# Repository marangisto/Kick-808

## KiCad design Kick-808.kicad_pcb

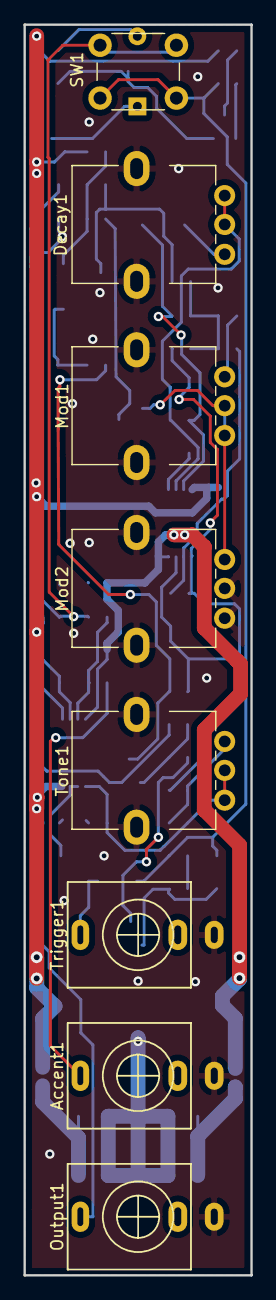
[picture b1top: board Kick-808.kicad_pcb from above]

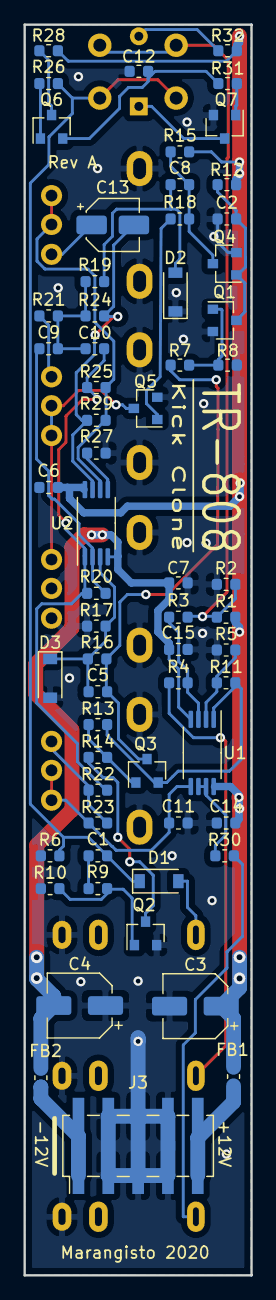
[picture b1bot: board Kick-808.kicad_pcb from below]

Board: 2 copper layers, 19.3 x 106.5 mm, 70 parts (62 on the bottom side), 42 nets.

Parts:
Accent1: AudioJack2_SwitchT; PJ398SM
C1, C2, C6, C7, C14, C15: 100n; C_0603_1608Metric
C3, C4: 22u; CP_Elec_5x5.4
C5, C9, C10: 15n; C_0603_1608Metric
C8: 33n; C_0603_1608Metric
C11: 22n; C_0603_1608Metric
C12: 1u; C_0603_1608Metric
C13: 10u; CP_Elec_4x5.8
D1, D2, D3: 1N4148; D_SOD-123
Decay1: 100k; AlpsRK09K
FB1, FB2: Ferrite_Bead; L_0603_1608Metric
J3: Conn_02x05_Odd_Even; PinHeader_2x05_P2.54mm_Vertical_SMD
Mod1: 10k; AlpsRK09K
Mod2: 100k; AlpsRK09K
Output1: AudioJack2_SwitchT; PJ398SM
Q1, Q2, Q4, Q5, Q6, Q7: BC847; SOT-23
Q3: BC857; SOT-23
R1: 2k2; R_0603_1608Metric
R2: 1k5; R_0603_1608Metric
R3: 200k; R_0603_1608Metric
R4, R31: 47k; R_0603_1608Metric
R5, R6, R11, R16, R18, R23, R26: 100k; R_0603_1608Metric
R7: 8k2; R_0603_1608Metric
R8: 2k7; R_0603_1608Metric
R9, R15: 22k; R_0603_1608Metric
R10, R14, R25, R29: 10k; R_0603_1608Metric
R12, R19, R20: 1M; R_0603_1608Metric
R13, R17, R27: 4k7; R_0603_1608Metric
R21, R28, R32: 1k; R_0603_1608Metric
R22: 220; R_0603_1608Metric
R24: 470k; R_0603_1608Metric
R30: 680; R_0603_1608Metric
SW1: SW_Push_LED; SW_PUSH_LED_6mm
Tone1: 100k; AlpsRK09K
Trigger1: AudioJack2_SwitchT; PJ398SM
U1, U2: TL072; TSSOP-8_4.4x3mm_P0.65mm

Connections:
5V: R1.2, R2.1, R3.2, SW1.1
+12V: C3.1, C6.2, C14.2, FB1.1, R1.1, R12.1, R15.1, R28.1, R32.1, U1.8, U2.8
-12V: C4.2, C7.1, C15.1, FB2.1, U1.4, U2.4
GND: Accent1.S, C2.2, C3.2, C4.1, C6.1, C7.2, C11.2, C12.2, C14.1, C15.2, D2.1, D3.2, J3.3, J3.4, J3.5, J3.6, J3.7, J3.8, Mod2.2, Mod2.3, Output1.S, Q1.2, Q2.2, Q4.2, Q5.2, Q7.2, R2.2, R5.2, R6.2, R8.1, R10.2, R17.2, R27.2, Trigger1.S
unnamed: Accent1.T, R4.2
unnamed: C1.1, R9.1
unnamed: C2.1, Q1.3, Q4.1, R12.2
unnamed: C5.1, D3.1, R16.1, R17.1, U2.3
unnamed: C5.2, Q3.3, R7.2, R16.2
unnamed: C8.1, D2.2, R19.2
unnamed: C8.2, Q4.3, R15.2, R18.2
unnamed: C9.2, R20.2, U2.2
unnamed: C10.1, R20.1, R22.1, R25.2, U2.1
unnamed: C9.1, C10.2, R19.1, R21.1, R24.2
unnamed: C11.1, R23.2, Tone1.2, Tone1.3, U1.5
unnamed: C12.1, Q6.2, R31.2
unnamed: C13.1, Decay1.3
unnamed: C13.2, R24.1, R29.1, U2.7
unnamed: D1.2, Trigger1.T
unnamed: Decay1.1, Decay1.2, R25.1, R29.2, U2.6
unnamed: FB1.2, J3.9, J3.10
unnamed: FB2.2, J3.1, J3.2
unnamed: Mod1.1, R21.2
unnamed: Mod1.2, Mod1.3, Mod2.1, Q5.3
unnamed: Output1.T, R30.1
unnamed: Q1.1, R7.1, R8.2
unnamed: Q2.1, R9.2, R10.1
unnamed: Q2.3, R14.2
unnamed: Q3.1, R13.2, R14.1
unnamed: Q3.2, R11.1, R13.1, U1.1
unnamed: Q5.1, R18.1
unnamed: Q6.1, R26.1
unnamed: Q6.3, R28.2
unnamed: Q7.1, R31.1
unnamed: Q7.3, SW1.4
unnamed: R3.1, R4.1, U1.3
unnamed: R5.1, R11.2, U1.2
unnamed: R22.2, R23.1, Tone1.1
unnamed: R27.1, U2.5
unnamed: R30.2, U1.6, U1.7
unnamed: R32.2, SW1.3
Pulse: C1.2, D1.1, R6.1, R26.2, SW1.2

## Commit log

2019-09-30 Added initial schematic based on http://www.ericarcher.net/wp-content/uploads/2014/07/tr-808-bass-drum-diy-project.pdf
2019-10-01 Added some footprints.
2019-10-03 Use film caps in audio path.
2020-07-07 Spice-verified design.
2020-07-10 Mods for output buffer, accent range and indicator.
2020-07-10 Corrected accent circuit.
2020-07-10 Augment decay stage for 100k pot.
2020-07-10 Augment tone stage for 100k pot and fix decay cap.
2020-07-10 Completed edits from spice to kicad.
2020-07-10 Corrected tone pot-value.
2020-07-11 PCB layout preparation.
2020-07-11 Use SMD pin header and get ready for placement.
2020-07-11 Use 2 dual op-amps for better layout.
2020-07-11 Outline placement.
2020-07-11 Initial placement on rear left-side.
2020-07-11 Initial placement on rear right-side.
2020-07-11 Added another rendering.
2020-07-11 Use symbolic path for local lib.
2020-07-11 Basic power routing.
2020-07-11 Ground pour on front.
2020-07-12 Routing almost complete.
2020-07-12 Routing completed.
2020-07-12 Routing adjustments.
2020-07-12 Front and rear silk-screen.
2020-07-12 Branding.
2020-07-12 Generated gerbers.
